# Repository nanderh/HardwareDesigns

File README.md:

HardwareDesigns
===============

A collection of PCB designs for various projects

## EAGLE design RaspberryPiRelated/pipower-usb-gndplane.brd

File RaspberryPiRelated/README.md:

## Raspberry Pi related PCBs
To connect multiple Pis to a single high current 5 Volt power supply I designed a simple distribution board to either 5 usb connectors or 5 screw terminals. Besides that there is space for smoothing capacitors, header connections to switch each connection separately, led indicators per connection and voltage test points.
Note: the main positive trace might seem quite large but it's designed for a maximum of 12A on a 1oz board.

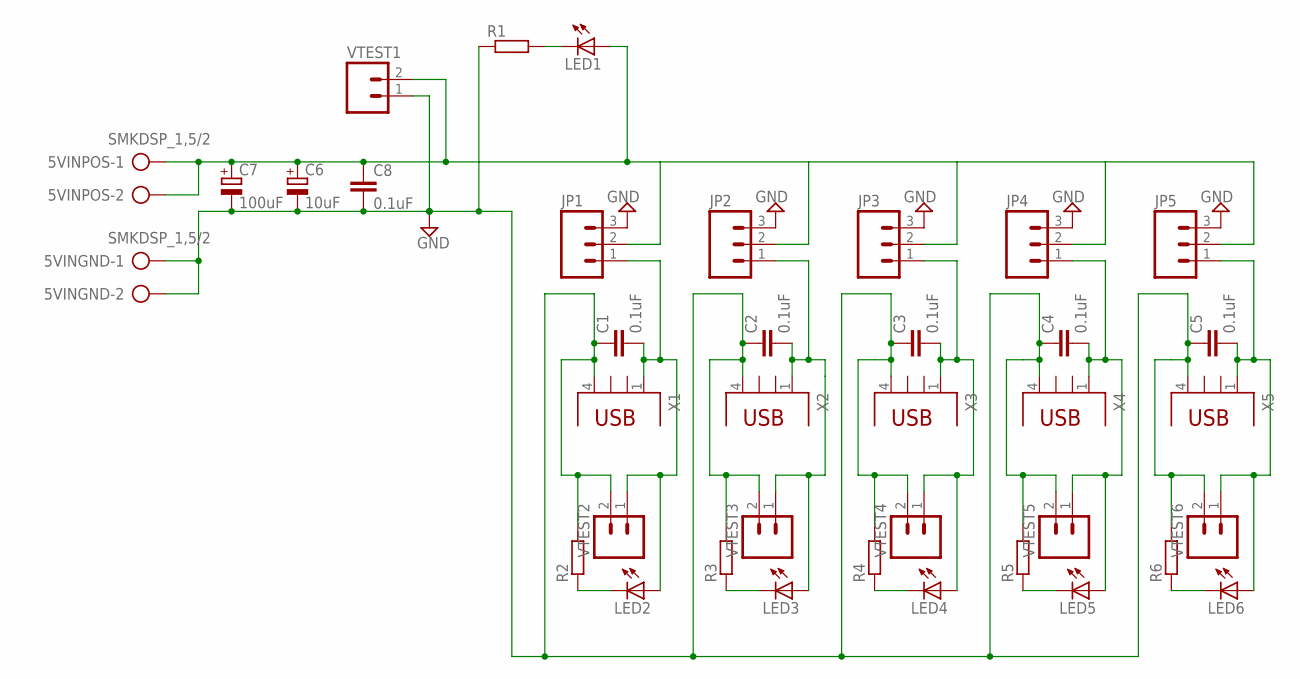
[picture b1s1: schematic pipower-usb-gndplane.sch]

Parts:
5VINGND, 5VINPOS: SMKDSP_1,5/2
C1, C2, C3, C4, C5, C8: 0.1uF; CAP-PTH-5MM
C6: 10uF; E5-10,5
C7: 100uF; E5-10,5
JP1, JP2, JP3, JP4, JP5: M03LONGPADS; 1X03_LONGPADS
LED1, LED2, LED3, LED4, LED5, LED6: LED5MM
R1, R2, R3, R4, R5, R6: R-EU_0207/12; 0207/12
VTEST1, VTEST2, VTEST3, VTEST4, VTEST5, VTEST6: M02PTH3; 1X02_LONGPADS
X1, X2, X3, X4, X5: PN87520

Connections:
GND: 5VINGND.1, 5VINGND.2, C1.1, C2.1, C3.1, C4.1, C5.1, C6.-, C7.-, C8.2, JP1.3, JP2.3, JP3.3, JP4.3, JP5.3, R1.1, R2.2, R3.2, R4.2, R5.2, R6.2, VTEST1.1, VTEST2.2, VTEST3.2, VTEST4.2, VTEST5.2, VTEST6.2, X1.4, X2.4, X3.4, X4.4, X5.4
MAINPOS: 5VINPOS.1, 5VINPOS.2, C6.+, C7.+, C8.1, JP1.2, JP2.2, JP3.2, JP4.2, JP5.2, LED1.A, VTEST1.2
unnamed: LED2.K (C), R2.1
unnamed: LED1.K (C), R1.2
unnamed: LED3.K (C), R3.1
unnamed: LED4.K (C), R4.1
unnamed: LED5.K (C), R5.1
unnamed: LED6.K (C), R6.1
POS1: C1.2, JP1.1, LED2.A, VTEST2.1, X1.1
POS2: C2.2, JP2.1, LED3.A, VTEST3.1, X2.1
POS3: C3.2, JP3.1, LED4.A, VTEST4.1, X3.1
POS4: C4.2, JP4.1, LED5.A, VTEST5.1, X4.1
POS5: C5.2, JP5.1, LED6.A, VTEST6.1, X5.1

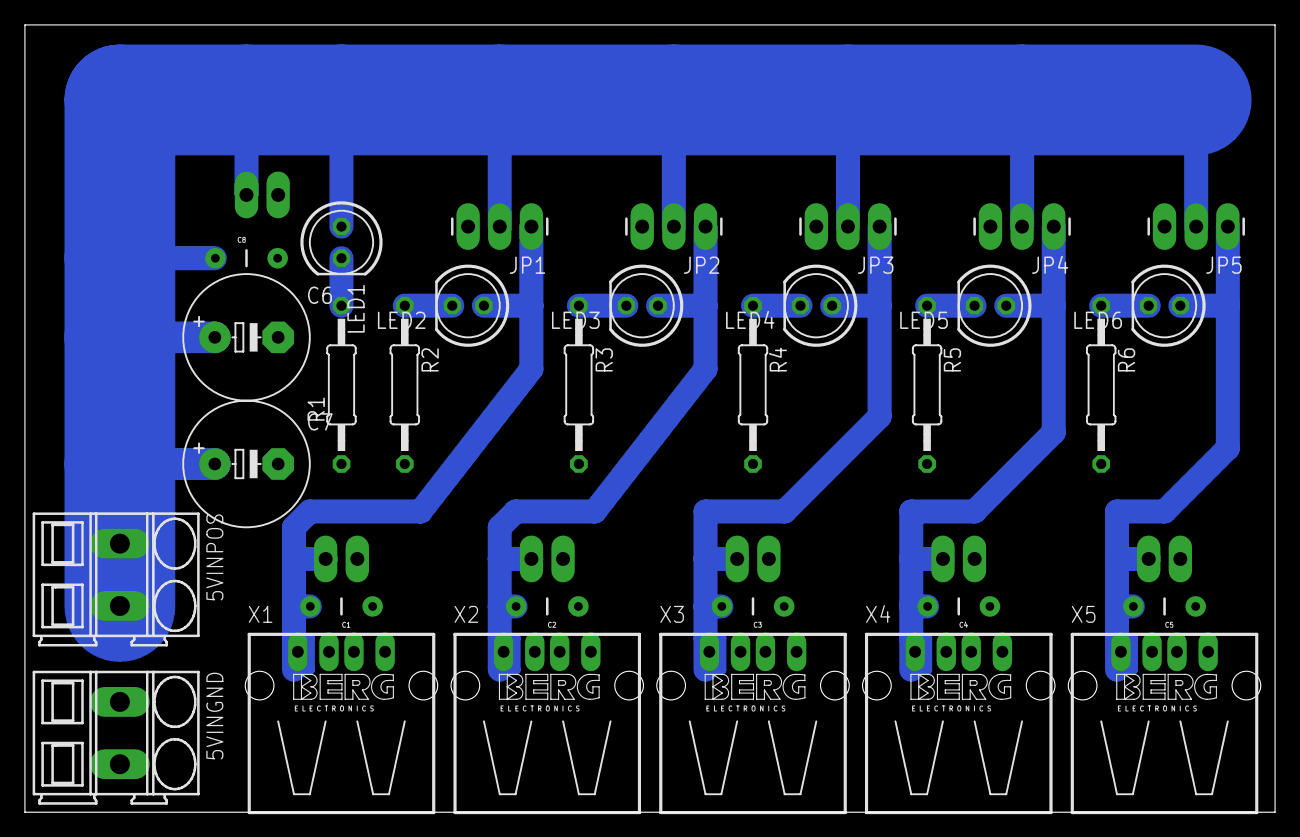
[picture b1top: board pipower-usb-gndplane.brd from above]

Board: 2 copper layers, 100.3 x 63.2 mm, 38 parts (0 on the bottom side), 13 nets.

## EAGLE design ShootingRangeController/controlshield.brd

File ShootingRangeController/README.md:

## Shooting Range Controller

This was a project for my local shooting range. 
It basically is a massive breakout board for the Arduino Mega with some smoothing capacitors and reverse voltage protection.
Then there are the relay drivers, the motors to drive the targets backwards and forwards were thee phase and needed 2 relays per motor. These relays were powered by their own 24 volt power supply.
I could not find the code for the Arduino but in a nutshell it was a continuous loop which constantly checked for changes in input and if it changed then drive or stop the motors appropriately.

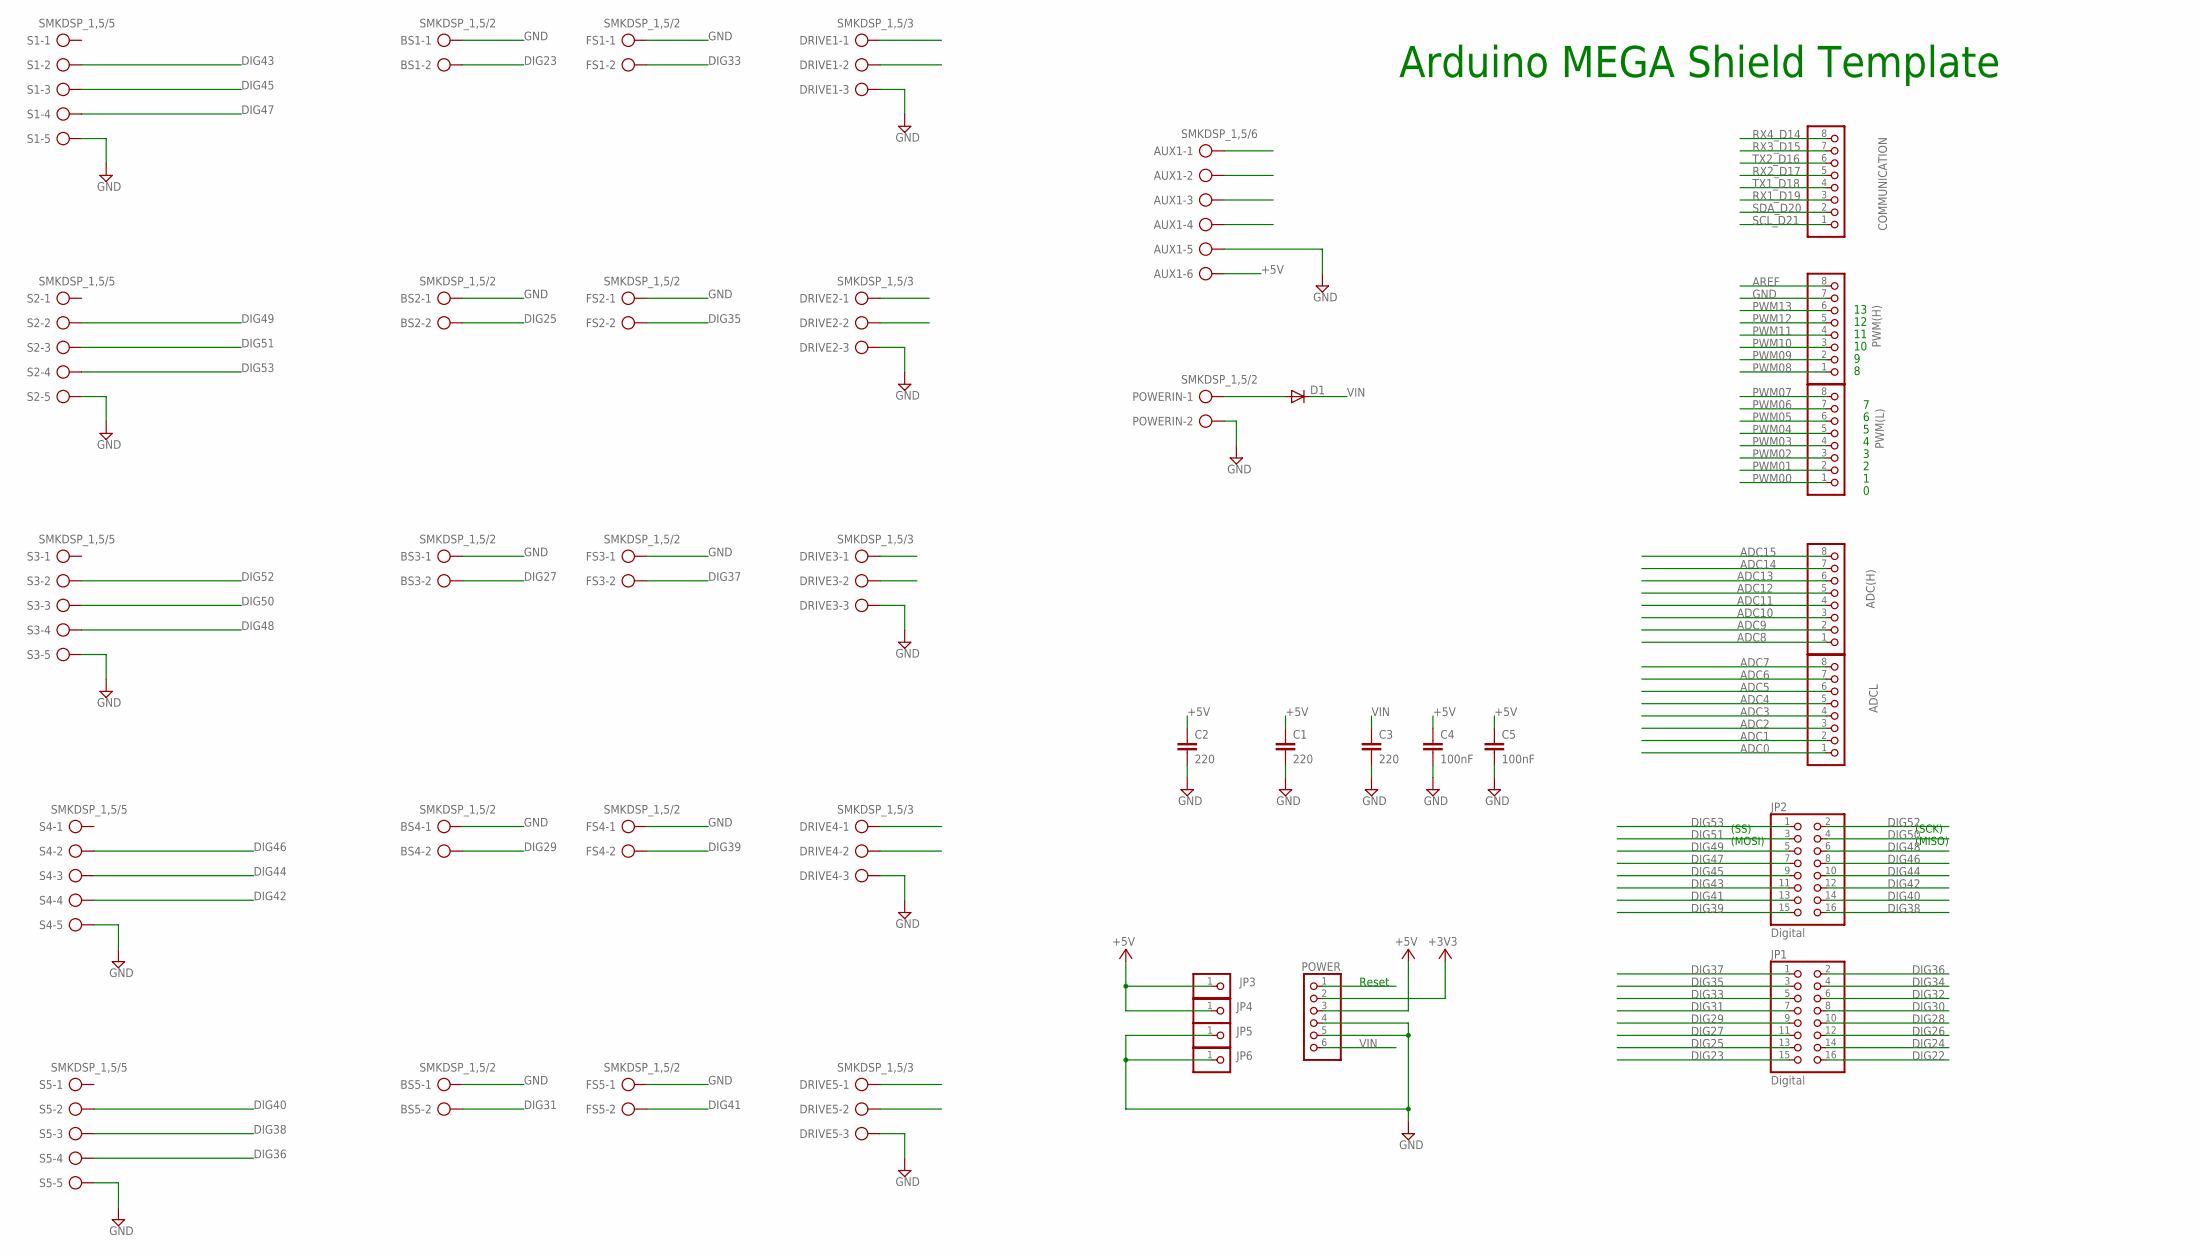
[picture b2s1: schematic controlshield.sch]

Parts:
ADC(H): PINHD-1X8; 1X08
ADCL: PINHD-1X8; 1X08
AUX1: SMKDSP_1,5/6
BS1, BS2, BS3, BS4, BS5: SMKDSP_1,5/2
C1, C2, C3: 220; C050-075X075
C4, C5: 100nF; CAP-PTH-5MM
COMMUNICATION: PINHD-1X8; 1X08
D1: DIODE-DO201-15; DO201-15
DRIVE1, DRIVE2, DRIVE3, DRIVE4, DRIVE5: SMKDSP_1,5/3
FS1, FS2, FS3, FS4, FS5: SMKDSP_1,5/2
JP1, JP2: Digital; 2X08
JP3, JP4, JP5, JP6: PINHD-1X1; 1X01
POWER: PINHD-1X6; 1X06
POWERIN: SMKDSP_1,5/2
PWM(H): PINHD-1X8; 1X08
PWM(L): PINHD-1X8; 1X08
S1, S2, S3, S4, S5: SMKDSP_1,5/5

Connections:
+3V3: POWER.2
+5V: AUX1.6, C1.1, C2.1, C4.1, C5.1, JP3.1, JP4.1, POWER.3
ADC0: ADCL.1
ADC1: ADCL.2
ADC2: ADCL.3
ADC3: ADCL.4
ADC4: ADCL.5
ADC5: ADCL.6
ADC6: ADCL.7
ADC7: ADCL.8
ADC8: ADC(H).1
ADC9: ADC(H).2
ADC10: ADC(H).3
ADC11: ADC(H).4
ADC12: ADC(H).5
ADC13: ADC(H).6
ADC14: ADC(H).7
ADC15: ADC(H).8
AREF: PWM(H).8
DIG22: DRIVE1.1, JP1.16
DIG23: BS1.2, JP1.15
DIG24: DRIVE1.2, JP1.14
DIG25: BS2.2, JP1.13
DIG26: DRIVE2.1, JP1.12
DIG27: BS3.2, JP1.11
DIG28: DRIVE2.2, JP1.10
DIG29: BS4.2, JP1.9
DIG30: JP1.8
DIG31: BS5.2, JP1.7
DIG32: JP1.6
DIG33: FS1.2, JP1.5
DIG34: JP1.4
DIG35: FS2.2, JP1.3
DIG36: JP1.2, S5.4
DIG37: FS3.2, JP1.1
DIG38: JP2.16, S5.3
DIG39: FS4.2, JP2.15
DIG40: JP2.14, S5.2
DIG41: FS5.2, JP2.13
DIG42: JP2.12, S4.4
DIG43: JP2.11, S1.2
DIG44: JP2.10, S4.3
DIG45: JP2.9, S1.3
DIG46: JP2.8, S4.2
DIG47: JP2.7, S1.4
DIG48: JP2.6, S3.4
DIG49: JP2.5, S2.2
DIG50: JP2.4, S3.3
DIG51: JP2.3, S2.3
DIG52: JP2.2, S3.2
DIG53: JP2.1, S2.4
GND: AUX1.5, BS1.1, BS2.1, BS3.1, BS4.1, BS5.1, C1.2, C2.2, C3.2, C4.2, C5.2, DRIVE1.3, DRIVE2.3, DRIVE3.3, DRIVE4.3, DRIVE5.3, FS1.1, FS2.1, FS3.1, FS4.1, FS5.1, JP5.1, JP6.1, POWER.4, POWER.5, POWERIN.2, PWM(H).7, S1.5, S2.5, S3.5, S4.5, S5.5
unnamed: D1.A, POWERIN.1
PWM00: PWM(L).1
PWM01: PWM(L).2
PWM02: PWM(L).3
PWM03: DRIVE3.1, PWM(L).4
PWM04: DRIVE3.2, PWM(L).5
PWM05: DRIVE4.1, PWM(L).6
PWM06: DRIVE4.2, PWM(L).7
PWM07: DRIVE5.1, PWM(L).8
PWM08: DRIVE5.2, PWM(H).1
PWM09: AUX1.1, PWM(H).2
PWM10: AUX1.2, PWM(H).3
PWM11: AUX1.3, PWM(H).4
PWM12: AUX1.4, PWM(H).5
PWM13: PWM(H).6
RESET: POWER.1
RX1_D19: COMMUNICATION.3
RX2_D17: COMMUNICATION.5
RX3_D15: COMMUNICATION.7
RX4_D14: COMMUNICATION.8
SCL_D21: COMMUNICATION.1
SDA_D20: COMMUNICATION.2
TX1_D18: COMMUNICATION.4
TX2_D16: COMMUNICATION.6
VIN: C3.1, D1.C, POWER.6

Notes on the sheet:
Arduino MEGA Shield Template
(SS)
(MOSI)
(SCK)
(MISO)
Reset

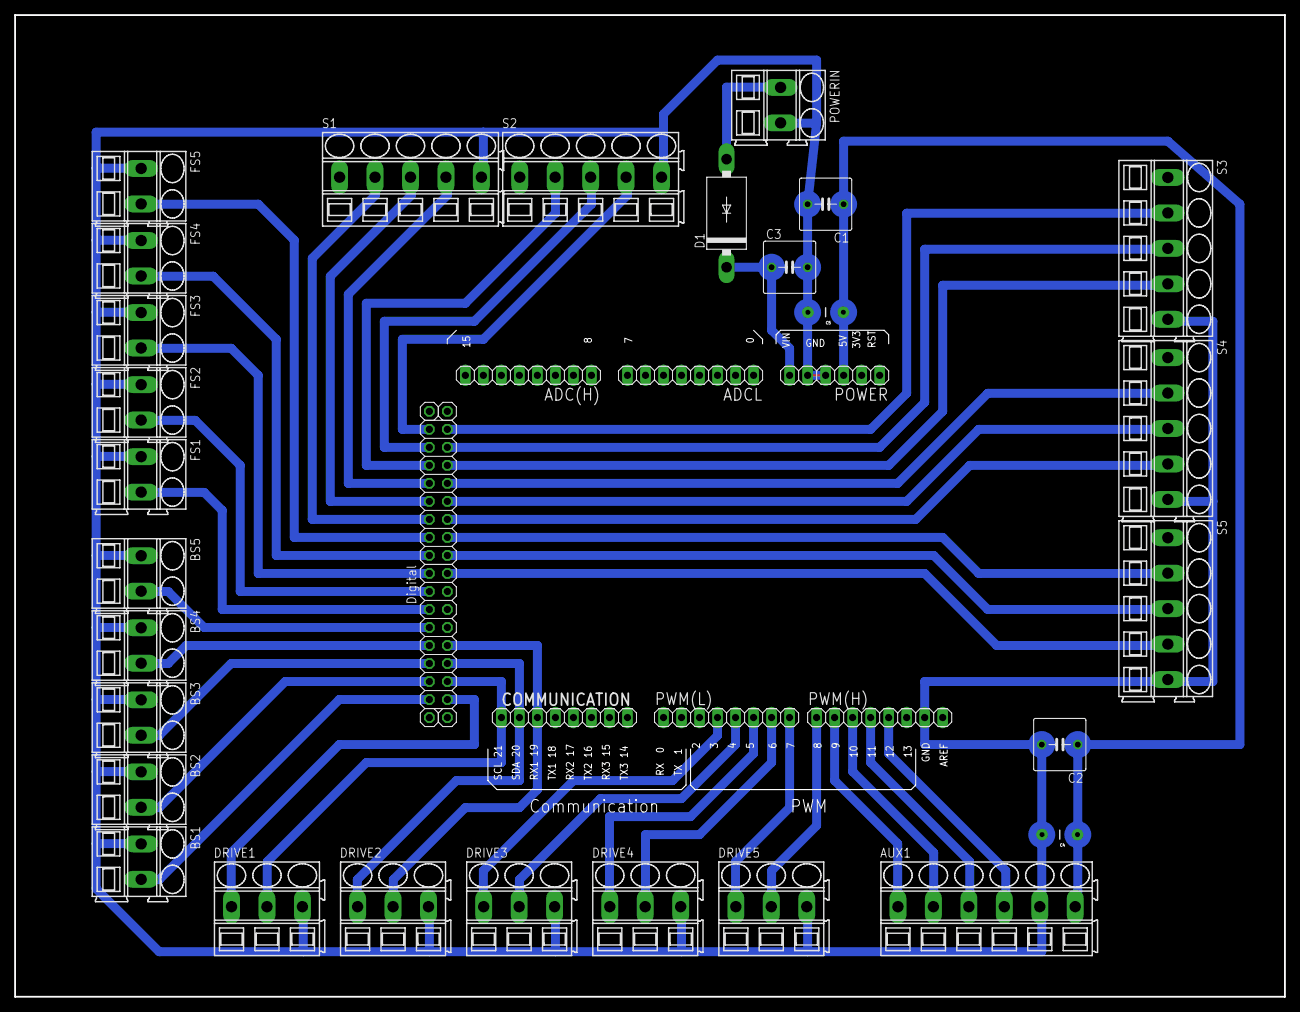
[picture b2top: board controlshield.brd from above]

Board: 2 copper layers, 179.1 x 138.4 mm, 40 parts (0 on the bottom side), 43 nets.

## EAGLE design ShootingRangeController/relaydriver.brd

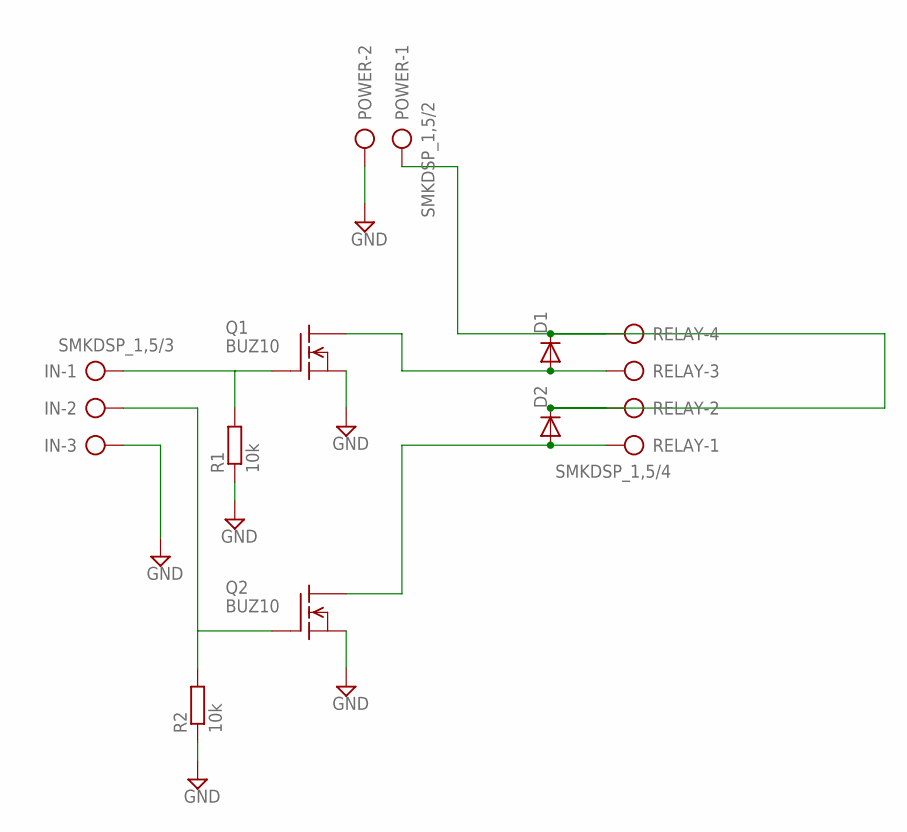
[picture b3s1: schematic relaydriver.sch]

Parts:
D1, D2: DIODE-DO201-15; DO201-15
IN: SMKDSP_1,5/3
POWER: SMKDSP_1,5/2
Q1, Q2: BUZ10; TO220
R1, R2: 10k; 0207/10
RELAY: SMKDSP_1,5/4

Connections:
GND: IN.3, POWER.2, Q1.3 (S), Q2.3 (S), R1.1, R2.1
IN1: IN.1, Q1.1 (G), R1.2
IN2: IN.2, Q2.1 (G), R2.2
R1-SINK: D1.A, Q1.2 (D), RELAY.3
R2-SINK: D2.A, Q2.2 (D), RELAY.1
R-DRIVE: D1.C, D2.C, POWER.1, RELAY.2, RELAY.4

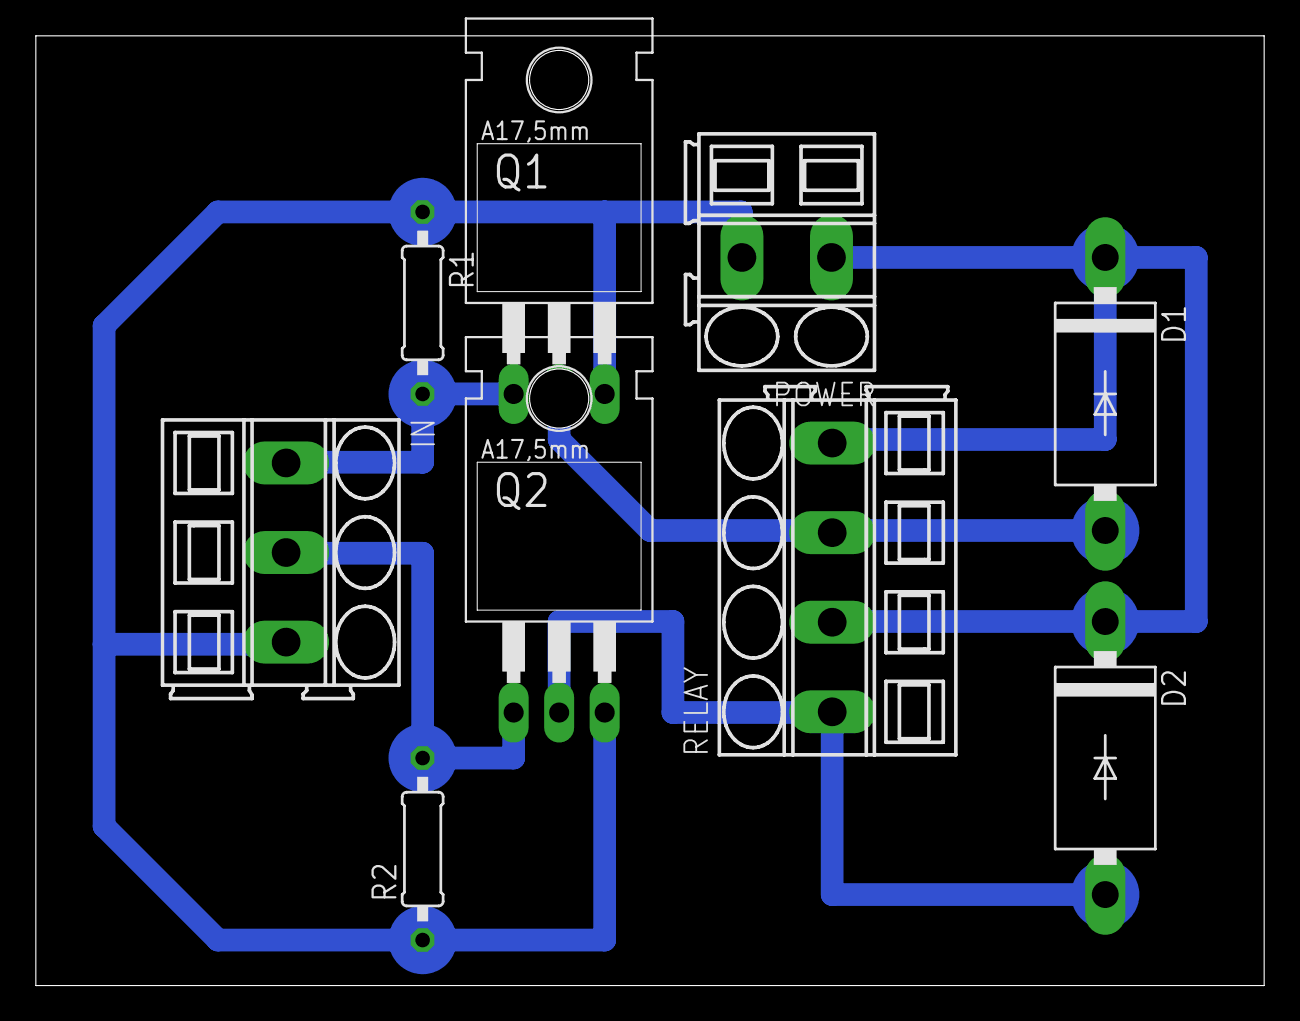
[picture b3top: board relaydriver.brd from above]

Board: 2 copper layers, 68.6 x 53.0 mm, 9 parts (0 on the bottom side), 6 nets.

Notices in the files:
parts and their libraries:
SparkFun-Capacitors: Licensing: CC v3.0 Share-Alike You are welcome to use this library for commercial purposes.
